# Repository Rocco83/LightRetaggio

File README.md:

# LightRetaggio

KiCad project for the LightRetaggioSchema board (LightController breakout), migrated from the original Eagle design.

## Repository layout

- `kicad/` — the active KiCad project (KiCad 10.0)
  - `LightRetaggioSchema.kicad_pro` — project file, open this in KiCad
  - `LightRetaggioSchema.kicad_sch` — schematic
  - `LightRetaggioSchema.kicad_pcb` — PCB layout
  - `LightRetaggioSchema-eagle-import.kicad_sym` — symbol library generated by the Eagle import
  - `LightRetaggioSchema.pretty/` — footprint library extracted from the imported board, registered in `fp-lib-table`
  - `sym-lib-table`, `fp-lib-table` — project-local library tables (paths are relative, no extra setup needed)
- `LightRetaggioSchema.sch` / `.brd` / `.pro` — original Eagle source (kept for reference)
- `LightRetaggioSchema_2020-04-23.zip` — archived Eagle export
- `eagle.epf` — Eagle workspace file

## Requirements

- [KiCad 10.0](https://www.kicad.org/download/) or newer

## Setup / build instructions

1. Install KiCad 10.0+.
2. Clone this repository:
   ```
   git clone https://github.com/Rocco83/LightRetaggio.git
   cd LightRetaggio
   ```
3. Open `kicad/LightRetaggioSchema.kicad_pro` in KiCad. The symbol and footprint libraries are referenced with relative paths in `sym-lib-table` / `fp-lib-table`, so no library setup is required beyond opening the project.
4. To edit: open the schematic (Eeschema) or PCB (Pcbnew) from the KiCad project manager.
5. To regenerate manufacturing outputs:
   - Gerbers/drill: Pcbnew → File → Fabrication Outputs → Gerbers / Drill Files
   - BOM: Eeschema → Tools → Generate Bill of Materials
   - Pick-and-place: Pcbnew → File → Fabrication Outputs → Component Placement Files

## Notes on the migration

The board was imported from the original Eagle source (rev V1.2, 2021-04-19) using KiCad's combined Eagle project importer. The importer generates a symbol library but no footprint library, so the footprints embedded in the imported board were extracted into `kicad/LightRetaggioSchema.pretty/` and registered under the `LightRetaggioSchema` nickname.

Verified clean after migration:
- **DRC**: 0 unconnected items, 0 footprint errors (remaining violations are cosmetic silkscreen/text sizing rules KiCad enforces more strictly than Eagle did)
- **ERC**: remaining violations are expected (unused switch pins, NC optocoupler pins, and a VCC/GND dual-net-naming convention already approved in the original Eagle file)

The original Eagle files (`.sch`, `.brd`, `.pro`) are kept at the repository root for reference/history.

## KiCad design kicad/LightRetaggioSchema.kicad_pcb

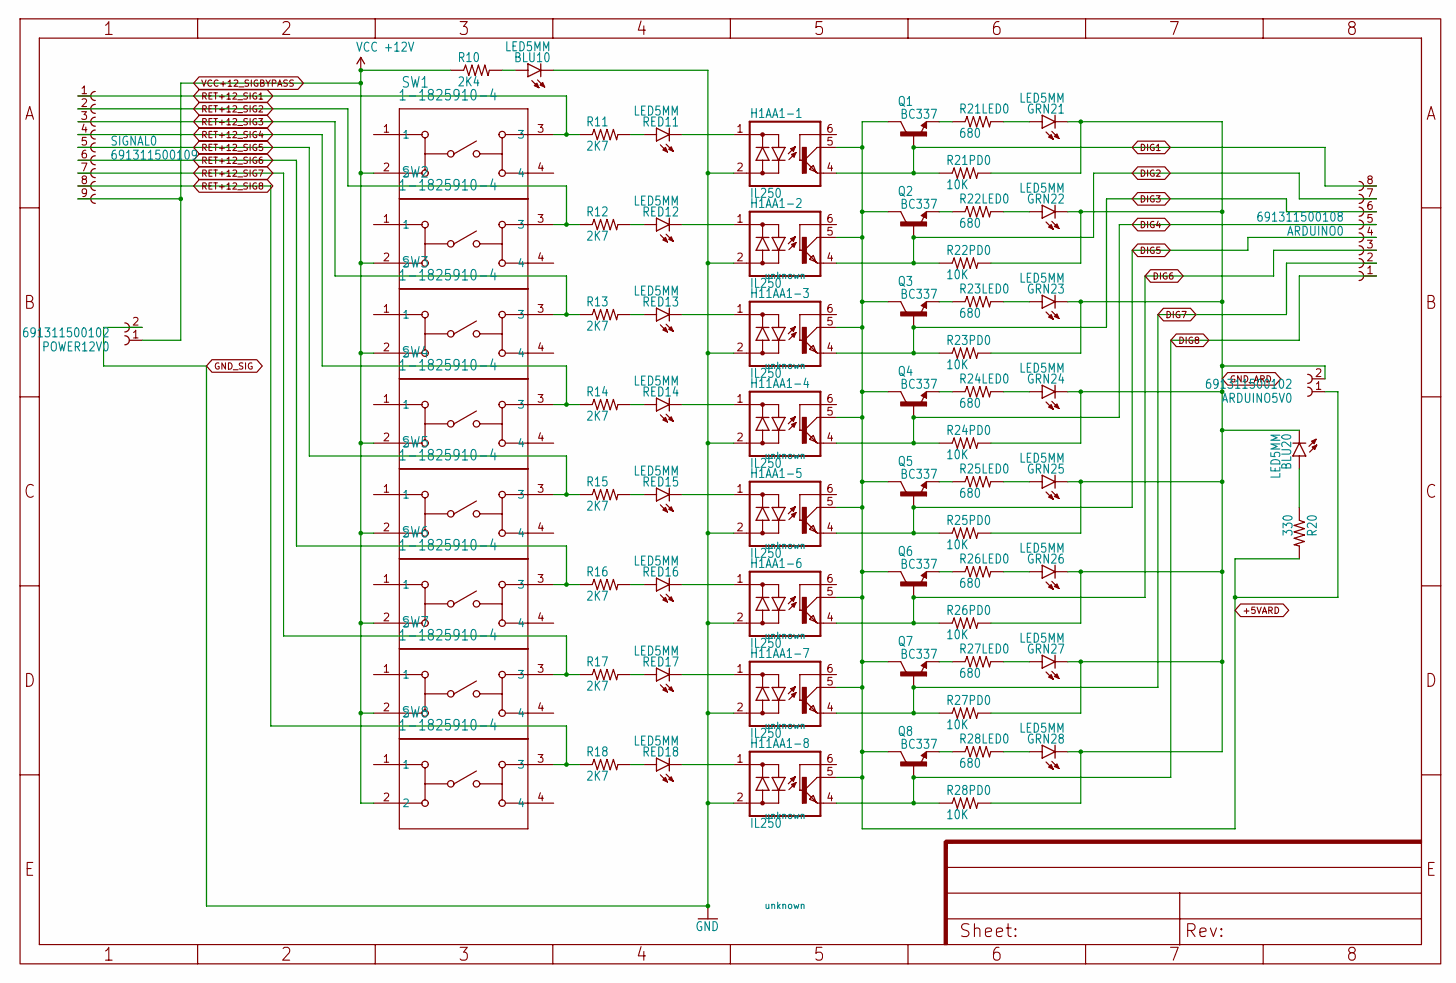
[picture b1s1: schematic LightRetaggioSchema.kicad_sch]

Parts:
ARDUINO0: 691311500108
ARDUINO5V0: 691311500102; MPN 691311500102
BLU10, BLU20: LED5MM; MPN FSM8JH
GRN21, GRN22, GRN23, GRN24, GRN25, GRN26, GRN27, GRN28: LED5MM; MPN FSM8JH
H1AA1-1, H1AA1-2, H1AA1-5, H1AA1-6, H11AA1-3, H11AA1-4, H11AA1-7, H11AA1-8: IL250; DIL06; MPN IL250
POWER12V0: 691311500102; MPN 691311500102
Q1, Q2, Q3, Q4, Q5, Q6, Q7, Q8: BC337; TO-92
R10: 2K4; AXIAL-0.4
R11, R12, R13, R14, R15, R16, R17, R18: 2K7; AXIAL-0.4
R20: 330; AXIAL-0.4
R21LED0, R22LED0, R23LED0, R24LED0, R25LED0, R26LED0, R27LED0, R28LED0: 680; AXIAL-0.4
R21PD0, R22PD0, R23PD0, R24PD0, R25PD0, R26PD0, R27PD0, R28PD0: 10K; AXIAL-0.4
RED11, RED12, RED13, RED14, RED15, RED16, RED17, RED18: LED5MM; MPN FSM8JH
SIGNAL0: 691311500109
SW1, SW2, SW3, SW4, SW5, SW6, SW7, SW8: 1-1825910-4; SW4_1825910-D; MANUFACTURER_PART_NUMBER 1-1825910-4

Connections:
+5VARD: ARDUINO5V0.1, H1AA1-1.5 (C), H1AA1-2.5 (C), H1AA1-5.5 (C), H1AA1-6.5 (C), H11AA1-3.5 (C), H11AA1-4.5 (C), H11AA1-7.5 (C), H11AA1-8.5 (C), Q1.1 (C), Q2.1 (C), Q3.1 (C), Q4.1 (C), Q5.1 (C), Q6.1 (C), Q7.1 (C), Q8.1 (C), R20.P$2 (2)
DIG1: ARDUINO0.8, H1AA1-1.4 (E), Q1.2 (B), R21PD0.P$1 (1)
DIG2: ARDUINO0.7, H1AA1-2.4 (E), Q2.2 (B), R22PD0.P$1 (1)
DIG3: ARDUINO0.6, H11AA1-3.4 (E), Q3.2 (B), R23PD0.P$1 (1)
DIG4: ARDUINO0.5, H11AA1-4.4 (E), Q4.2 (B), R24PD0.P$1 (1)
DIG5: ARDUINO0.4, H1AA1-5.4 (E), Q5.2 (B), R25PD0.P$1 (1)
DIG6: ARDUINO0.3, H1AA1-6.4 (E), Q6.2 (B), R26PD0.P$1 (1)
DIG7: ARDUINO0.2, H11AA1-7.4 (E), Q7.2 (B), R27PD0.P$1 (1)
DIG8: ARDUINO0.1, H11AA1-8.4 (E), Q8.2 (B), R28PD0.P$1 (1)
GND_ARD: ARDUINO5V0.2, BLU20.K (C), GRN21.K (C), GRN22.K (C), GRN23.K (C), GRN24.K (C), GRN25.K (C), GRN26.K (C), GRN27.K (C), GRN28.K (C), R21PD0.P$2 (2), R22PD0.P$2 (2), R23PD0.P$2 (2), R24PD0.P$2 (2), R25PD0.P$2 (2), R26PD0.P$2 (2), R27PD0.P$2 (2), R28PD0.P$2 (2)
GND_SIG: BLU10.K (C), H1AA1-1.2 (AC2), H1AA1-2.2 (AC2), H1AA1-5.2 (AC2), H1AA1-6.2 (AC2), H11AA1-3.2 (AC2), H11AA1-4.2 (AC2), H11AA1-7.2 (AC2), H11AA1-8.2 (AC2), POWER12V0.2
unnamed: BLU10.A, R10.P$2 (2)
unnamed: BLU20.A, R20.P$1 (1)
unnamed: H11AA1-8.1 (AC1), RED18.K (C)
unnamed: H11AA1-7.1 (AC1), RED17.K (C)
unnamed: H1AA1-6.1 (AC1), RED16.K (C)
unnamed: H1AA1-5.1 (AC1), RED15.K (C)
unnamed: Q1.3 (E), R21LED0.P$1 (1)
unnamed: GRN21.A, R21LED0.P$2 (2)
unnamed: H11AA1-4.1 (AC1), RED14.K (C)
unnamed: Q2.3 (E), R22LED0.P$1 (1)
unnamed: GRN22.A, R22LED0.P$2 (2)
unnamed: Q3.3 (E), R23LED0.P$1 (1)
unnamed: GRN23.A, R23LED0.P$2 (2)
unnamed: Q4.3 (E), R24LED0.P$1 (1)
unnamed: GRN24.A, R24LED0.P$2 (2)
unnamed: R13.P$2 (2), RED13.A
unnamed: H11AA1-3.1 (AC1), RED13.K (C)
unnamed: R14.P$2 (2), RED14.A
unnamed: R12.P$2 (2), RED12.A
unnamed: R11.P$2 (2), RED11.A
unnamed: R17.P$2 (2), RED17.A
unnamed: R18.P$2 (2), RED18.A
unnamed: R16.P$2 (2), RED16.A
unnamed: R15.P$2 (2), RED15.A
unnamed: Q5.3 (E), R25LED0.P$1 (1)
unnamed: GRN25.A, R25LED0.P$2 (2)
unnamed: Q6.3 (E), R26LED0.P$1 (1)
unnamed: GRN26.A, R26LED0.P$2 (2)
unnamed: Q7.3 (E), R27LED0.P$1 (1)
unnamed: GRN27.A, R27LED0.P$2 (2)
unnamed: Q8.3 (E), R28LED0.P$1 (1)
unnamed: GRN28.A, R28LED0.P$2 (2)
unnamed: H1AA1-2.1 (AC1), RED12.K (C)
unnamed: H1AA1-1.1 (AC1), RED11.K (C)
RET+12_SIG1: R11.P$1 (1), SIGNAL0.1, SW1.3
RET+12_SIG2: R12.P$1 (1), SIGNAL0.2, SW2.3
RET+12_SIG3: R13.P$1 (1), SIGNAL0.3, SW3.3
RET+12_SIG4: R14.P$1 (1), SIGNAL0.4, SW4.3
RET+12_SIG5: R15.P$1 (1), SIGNAL0.5, SW5.3
RET+12_SIG6: R16.P$1 (1), SIGNAL0.6, SW6.3
RET+12_SIG7: R17.P$1 (1), SIGNAL0.7, SW7.3
RET+12_SIG8: R18.P$1 (1), SIGNAL0.8, SW8.3
VCC+12_SIGBYPASS: POWER12V0.1, R10.P$1 (1), SIGNAL0.9, SW1.2, SW2.2, SW3.2, SW4.2, SW5.2, SW6.2, SW7.2, SW8.2

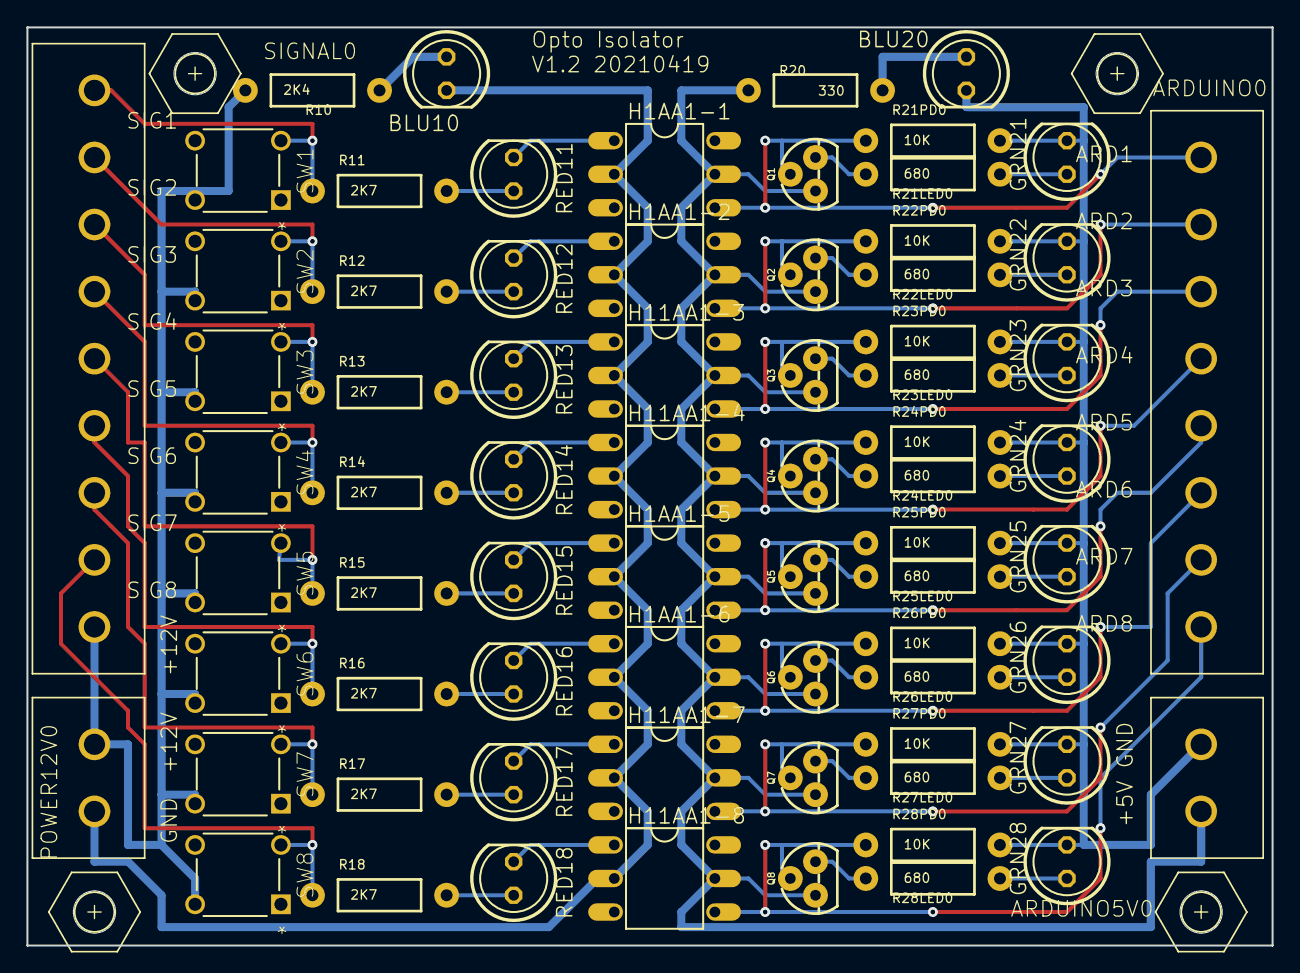
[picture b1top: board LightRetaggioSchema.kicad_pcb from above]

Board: 2 copper layers, 94.3 x 69.5 mm, 80 parts (0 on the bottom side), 54 nets.

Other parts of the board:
U$1, U$2, U$3, U$5: M3.0_SW6.0
UNK_HOLE_0: dummyfp0
UNK_HOLE_1: dummyfp1
UNK_HOLE_2: dummyfp2
UNK_HOLE_3: dummyfp3

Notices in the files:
parts and their libraries:
COPYRIGHT: Copyright (C) 2016 Accelerated Designs. All rights reserved
